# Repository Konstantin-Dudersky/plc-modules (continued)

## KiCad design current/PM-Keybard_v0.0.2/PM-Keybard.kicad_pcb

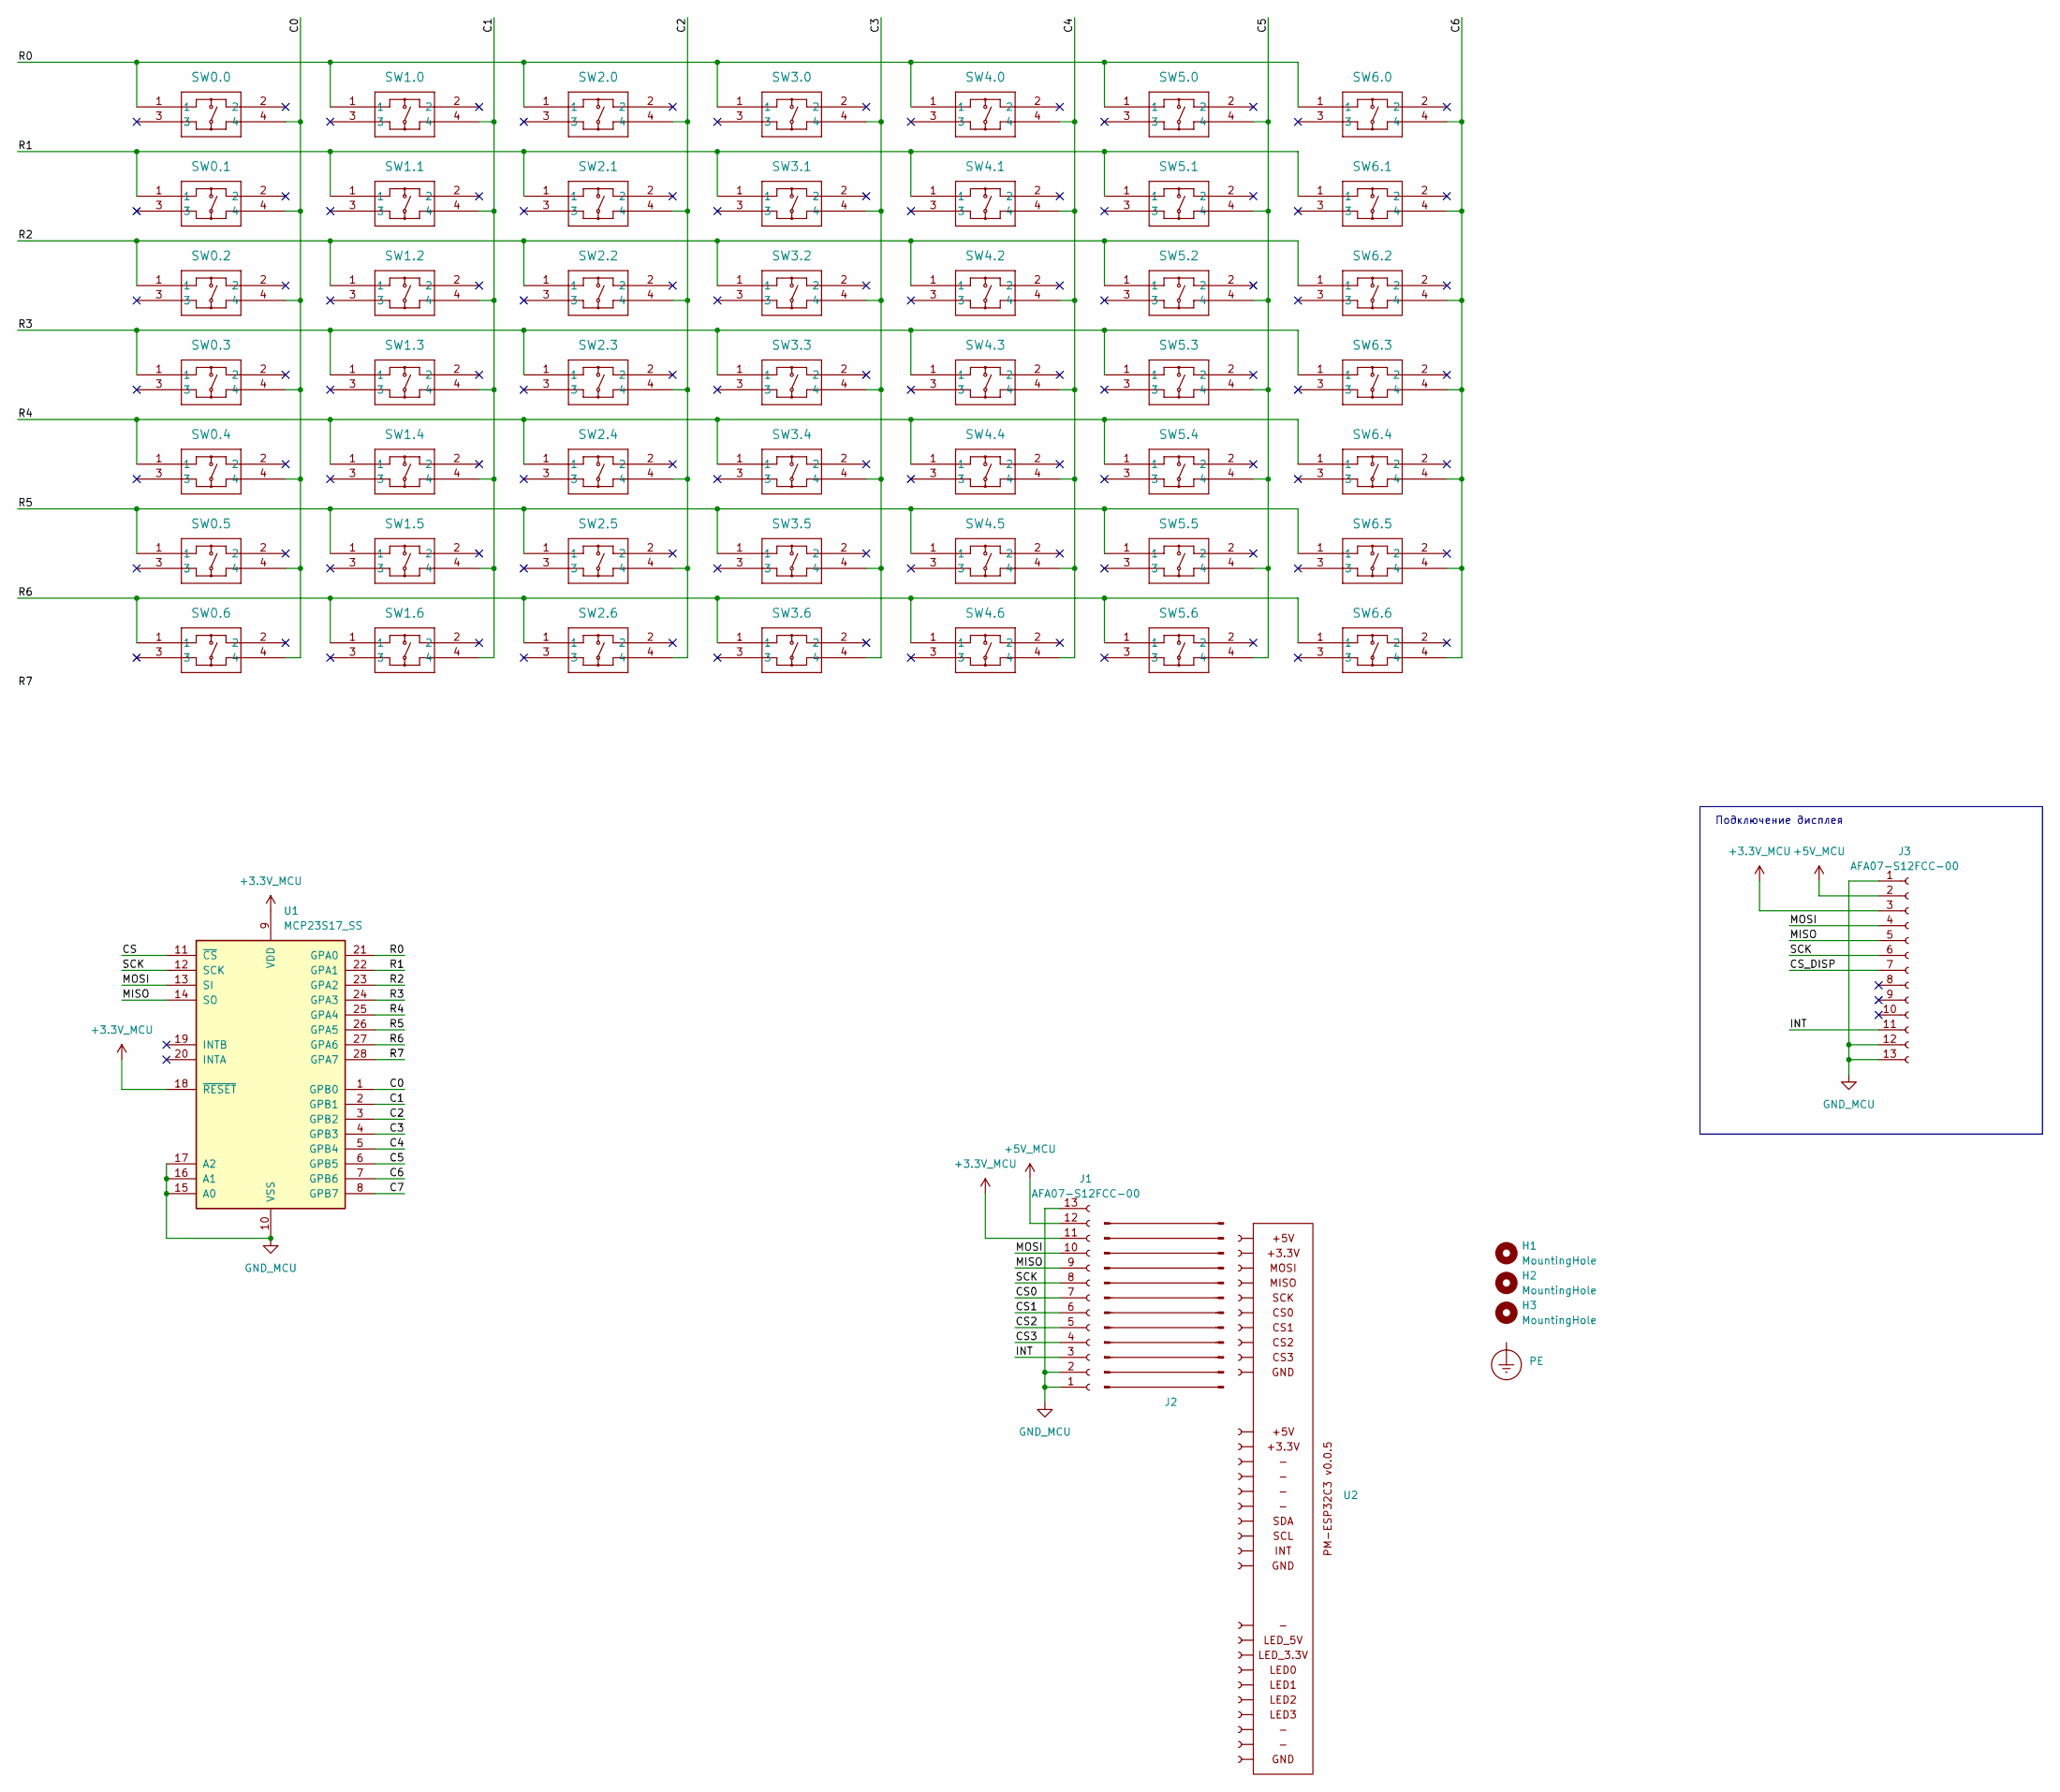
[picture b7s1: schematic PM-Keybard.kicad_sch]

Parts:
H1, H2, H3: MountingHole; MountingHole_3.2mm_M3
J1, J3: AFA07-S12FCC-00; CONN10_AFA07-S12_JUS; part_ipn AFA07-S12FCC-00
J2: FFC_12P_P1.0_100mm_straight; part_ipn FFC_12P_P1.0_100mm_straight
PE1: PE
SW0.0, SW0.1, SW0.2, SW0.3, SW0.4, SW0.5, SW0.6, SW1.0, SW1.1, SW1.2, SW1.3, SW1.4, SW1.5, SW1.6, SW2.0, SW2.1, SW2.2, SW2.3, SW2.4, SW2.5, SW2.6, SW3.0, SW3.1, SW3.2, SW3.3, SW3.4, SW3.5, SW3.6, SW4.0, SW4.1, SW4.2, SW4.3, SW4.4, SW4.5, SW4.6, SW5.0, SW5.1, SW5.2, SW5.3, SW5.4, SW5.5, SW5.6, SW6.0, SW6.1, SW6.2, SW6.3, SW6.4, SW6.5, SW6.6: TS-1187A-B-A-B; TS-1187A-B-A-B_XKB; part_ipn TS-1187A-B-A-B
U1: MCP23S17_SS; SSOP28_MC_MCH; part_ipn MCP23S17-E/SS
U2: PM-ESP32C3_v0.0.5; part_ipn PM_MCU-ESP32_C3-v0.0.5

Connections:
+3.3V_MCU: J1.11, J3.3, U1.9 (VDD), U1.18 (~RESET)
+5V_MCU: J1.12 (Pin_11), J3.2
/C0: SW0.0.4, SW0.1.4, SW0.2.4, SW0.3.4, SW0.4.4, SW0.5.4, SW0.6.4, U1.1 (GPB0)
/C1: SW1.0.4, SW1.1.4, SW1.2.4, SW1.3.4, SW1.4.4, SW1.5.4, SW1.6.4, U1.2 (GPB1)
/C2: SW2.0.4, SW2.1.4, SW2.2.4, SW2.3.4, SW2.4.4, SW2.5.4, SW2.6.4, U1.3 (GPB2)
/C3: SW3.0.4, SW3.1.4, SW3.2.4, SW3.3.4, SW3.4.4, SW3.5.4, SW3.6.4, U1.4 (GPB3)
/C4: SW4.0.4, SW4.1.4, SW4.2.4, SW4.3.4, SW4.4.4, SW4.5.4, SW4.6.4, U1.5 (GPB4)
/C5: SW5.0.4, SW5.1.4, SW5.2.4, SW5.3.4, SW5.4.4, SW5.5.4, SW5.6.4, U1.6 (GPB5)
/C6: SW6.0.4, SW6.1.4, SW6.2.4, SW6.3.4, SW6.4.4, SW6.5.4, SW6.6.4, U1.7 (GPB6)
/C7: U1.8 (GPB7)
/CS: U1.11 (~CS)
/CS0: J1.7
/CS1: J1.6
/CS2: J1.5
/CS3: J1.4
/CS_DISP: J3.7
/INT: J1.3, J3.11
/MISO: J1.9, J3.5, U1.14 (SO)
/MOSI: J1.10, J3.4, U1.13 (SI)
/R0: SW0.0.1, SW1.0.1, SW2.0.1, SW3.0.1, SW4.0.1, SW5.0.1, SW6.0.1, U1.21 (GPA0)
/R1: SW0.1.1, SW1.1.1, SW2.1.1, SW3.1.1, SW4.1.1, SW5.1.1, SW6.1.1, U1.22 (GPA1)
/R2: SW0.2.1, SW1.2.1, SW2.2.1, SW3.2.1, SW4.2.1, SW5.2.1, SW6.2.1, U1.23 (GPA2)
/R3: SW0.3.1, SW1.3.1, SW2.3.1, SW3.3.1, SW4.3.1, SW5.3.1, SW6.3.1, U1.24 (GPA3)
/R4: SW0.4.1, SW1.4.1, SW2.4.1, SW3.4.1, SW4.4.1, SW5.4.1, SW6.4.1, U1.25 (GPA4)
/R5: SW0.5.1, SW1.5.1, SW2.5.1, SW3.5.1, SW4.5.1, SW5.5.1, SW6.5.1, U1.26 (GPA5)
/R6: SW0.6.1, SW1.6.1, SW2.6.1, SW3.6.1, SW4.6.1, SW5.6.1, SW6.6.1, U1.27 (GPA6)
/R7: U1.28 (GPA7)
/SCK: J1.8, J3.6, U1.12 (SCK)
GND_MCU: J1.1, J1.2, J1.13 (Pin_11), J3.1, J3.12 (Pin_11), J3.13 (Pin_11), U1.10 (VSS), U1.15 (A0), U1.16 (A1), U1.17 (A2)

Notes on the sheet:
Подключение дисплея

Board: 2 copper layers, 57 parts (49 on the bottom side), 21 nets, no tracks yet.

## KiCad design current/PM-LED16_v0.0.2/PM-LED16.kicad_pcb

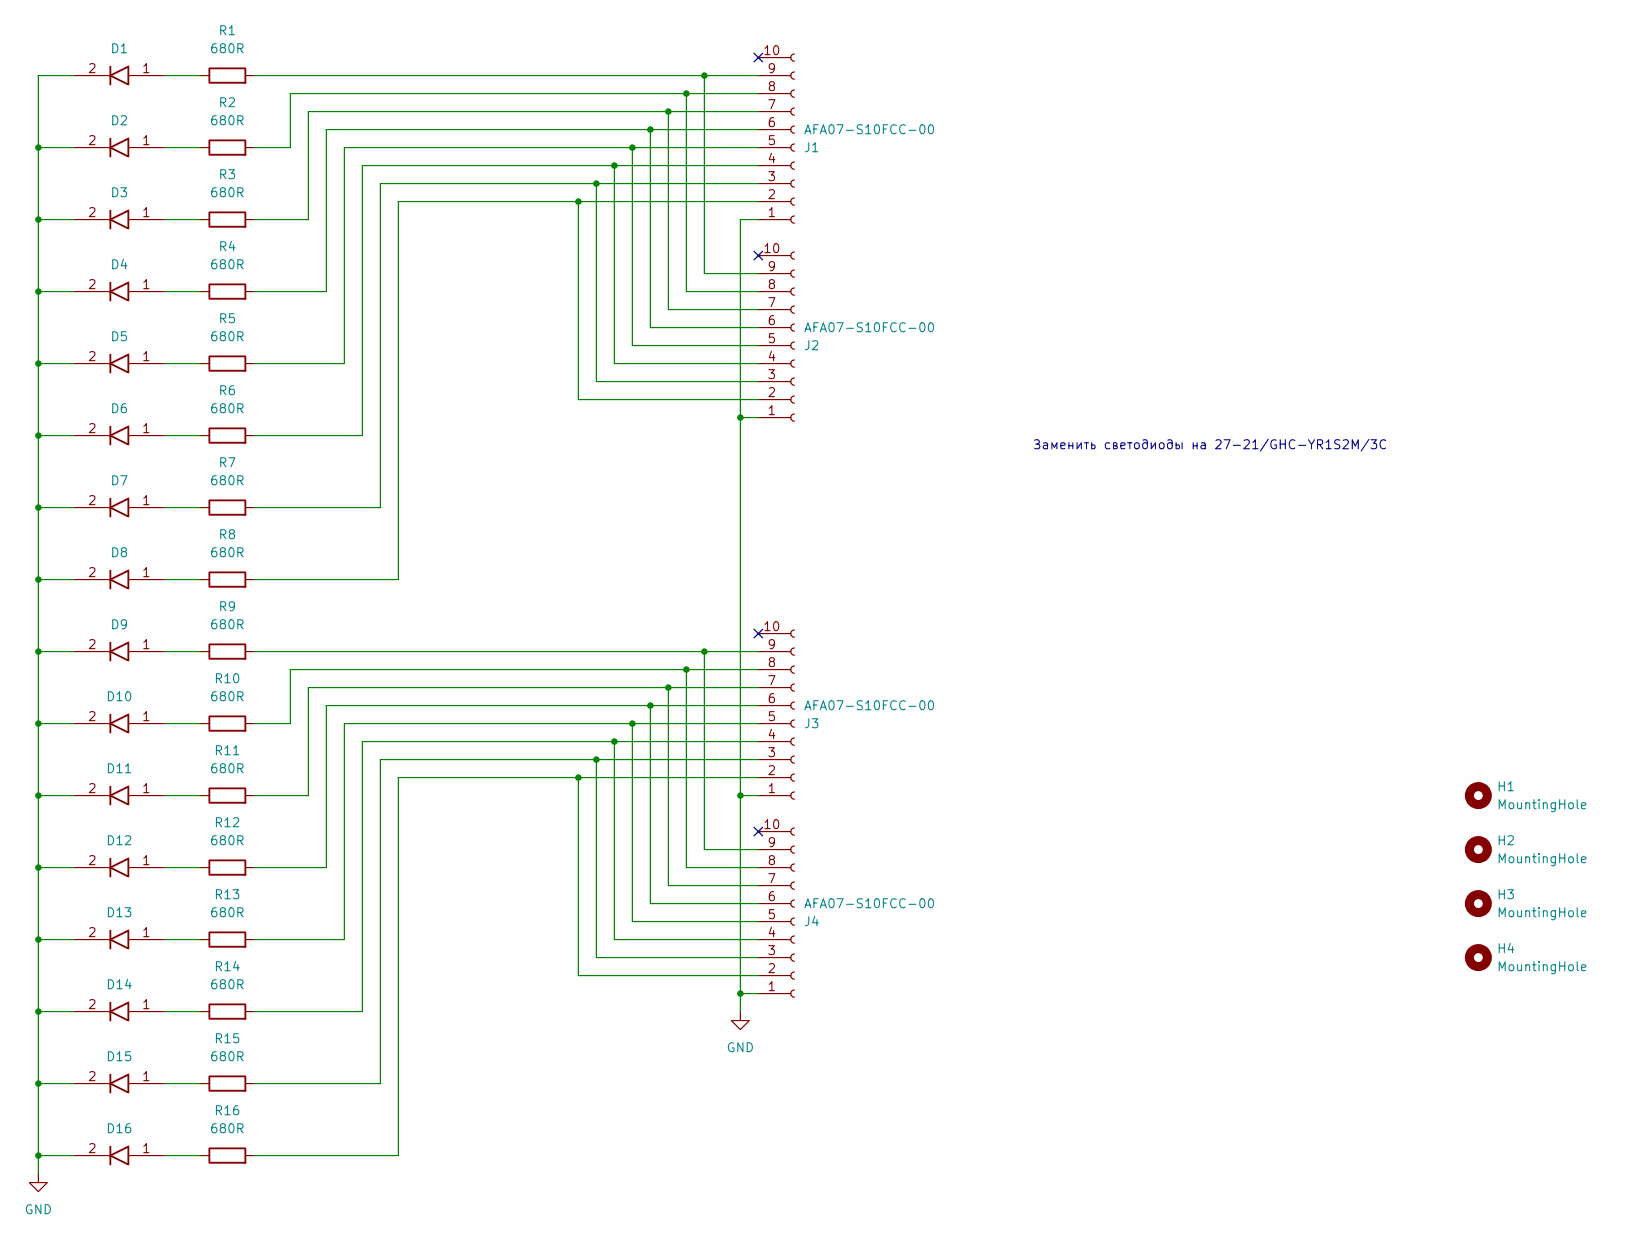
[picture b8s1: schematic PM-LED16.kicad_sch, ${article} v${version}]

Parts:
D1, D2, D3, D4, D5, D6, D7, D8, D9, D10, D11, D12, D13, D14, D15, D16: 12-21_GHC-YR2S2_2C; 1221GHCYR2S22C; part_ipn 12-21/GHC-YR2S2/2C
H1, H2, H3, H4: MountingHole; MountingHole_2.2mm_M2
J1, J2, J3, J4: AFA07-S10FCC-00; CONN10_AFA07-S10_JUS; part_ipn AFA07-S10FCC-00
R1, R2, R3, R4, R5, R6, R7, R8, R9, R10, R11, R12, R13, R14, R15, R16: 680R; R_1206_3216Metric_Pad1.30x1.75mm_HandSolder; part_ipn R_680R_1206_1%

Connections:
GND: D1.2, D2.2, D3.2, D4.2, D5.2, D6.2, D7.2, D8.2, D9.2, D10.2, D11.2, D12.2, D13.2, D14.2, D15.2, D16.2, J1.1, J2.1, J3.1, J4.1
unnamed: D1.1, R1.1
unnamed: D2.1, R2.1
unnamed: D3.1, R3.1
unnamed: D4.1, R4.1
unnamed: D5.1, R5.1
unnamed: D6.1, R6.1
unnamed: D7.1, R7.1
unnamed: D8.1, R8.1
unnamed: D9.1, R9.1
unnamed: D10.1, R10.1
unnamed: D11.1, R11.1
unnamed: D12.1, R12.1
unnamed: D13.1, R13.1
unnamed: D14.1, R14.1
unnamed: D15.1, R15.1
unnamed: D16.1, R16.1
unnamed: J1.2, J2.2, R8.2
unnamed: J1.3, J2.3, R7.2
unnamed: J1.4, J2.4, R6.2
unnamed: J1.5, J2.5, R5.2
unnamed: J1.6, J2.6, R4.2
unnamed: J1.7, J2.7, R3.2
unnamed: J1.8, J2.8, R2.2
unnamed: J1.9, J2.9, R1.2
unnamed: J3.2, J4.2, R16.2
unnamed: J3.3, J4.3, R15.2
unnamed: J3.4, J4.4, R14.2
unnamed: J3.5, J4.5, R13.2
unnamed: J3.6, J4.6, R12.2
unnamed: J3.7, J4.7, R11.2
unnamed: J3.8, J4.8, R10.2
unnamed: J3.9, J4.9, R9.2

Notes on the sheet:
Заменить светодиоды на 27-21/GHC-YR1S2M/3C

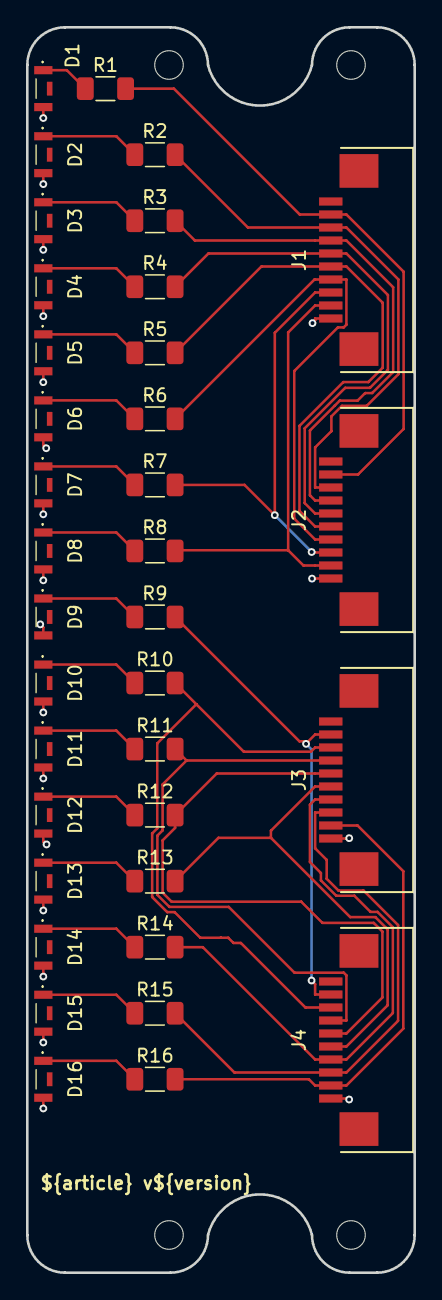
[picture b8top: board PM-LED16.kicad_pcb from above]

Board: 2 copper layers, 29.8 x 95.8 mm, 41 parts (1 on the bottom side), 33 nets.

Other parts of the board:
Logo_kicad: KiCad-Logo2_5mm_SilkScreen
